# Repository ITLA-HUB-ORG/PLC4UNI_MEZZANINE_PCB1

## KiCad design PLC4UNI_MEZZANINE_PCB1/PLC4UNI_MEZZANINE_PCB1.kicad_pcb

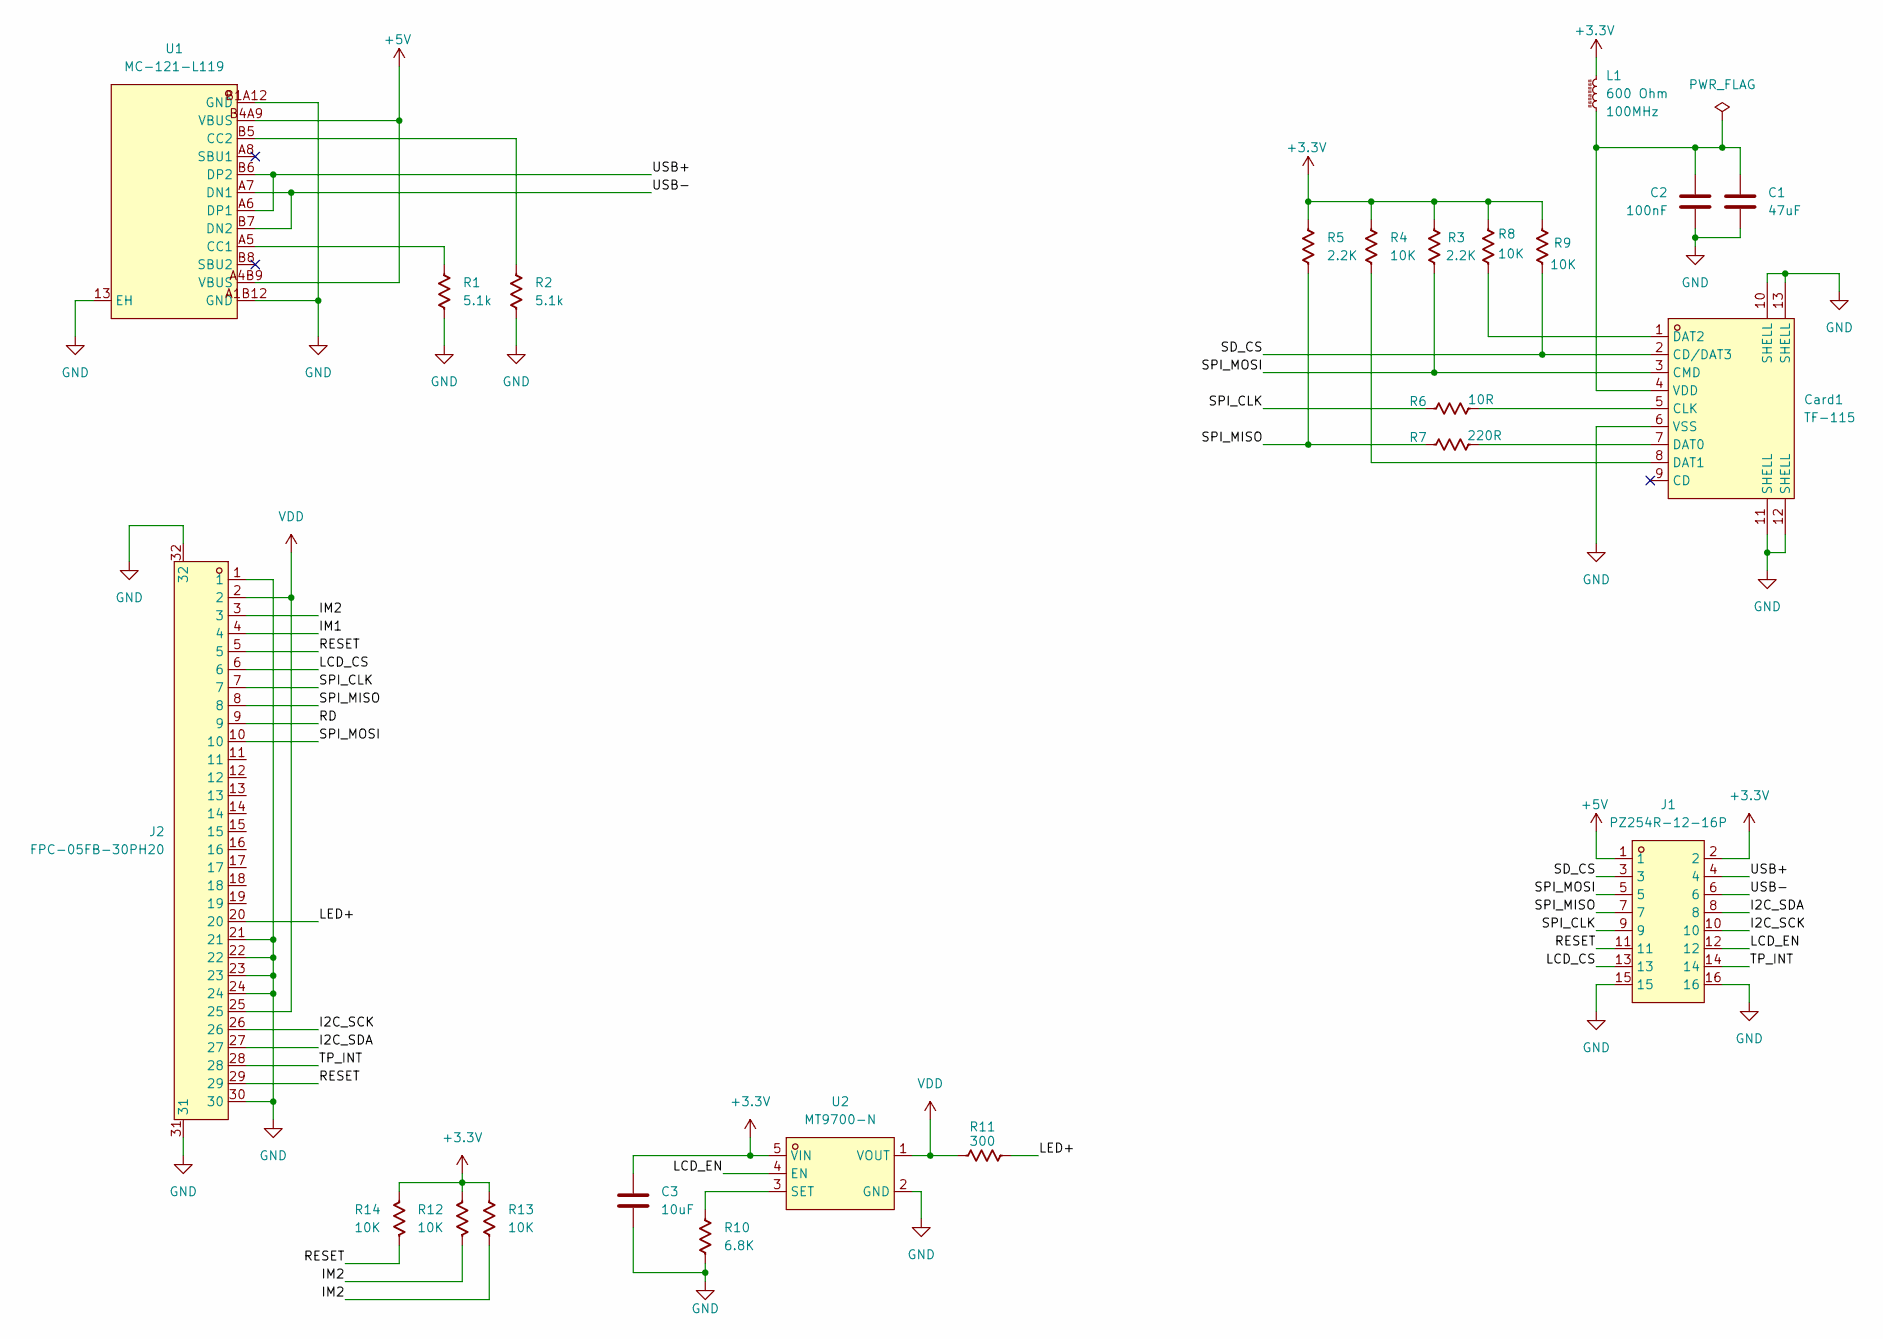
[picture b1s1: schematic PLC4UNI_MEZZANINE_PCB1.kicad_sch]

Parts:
C1: 47uF; C_0603_1608Metric
C2: 100nF; C_0603_1608Metric
C3: 10uF; C_0603_1608Metric
Card1: TF-115; TF-SMD_TF-115; LCSC Part C266620
J1: PZ254R-12-16P; HDR-TH_16P-P2.54-H-M-R2-C8-S2.54; LCSC Part C492436
J2: FPC-05FB-30PH20; FPC-SMD_30P-P0.50_FPC-05FB-30PH20; LCSC Part C2856833
L1: 600 Ohm; C_0805_2012Metric
R1, R2: 5.1k; R_0603_1608Metric
R3, R5: 2.2K; R_0603_1608Metric
R4, R8, R9, R12, R13, R14: 10K; R_0603_1608Metric
R6: 10R; R_0603_1608Metric
R7: 220R; R_0603_1608Metric
R10: 6.8K; R_0603_1608Metric
R11: 300; R_0603_1608Metric
U1: MC-121-L119; USB-C-SMD_HANBO_MC-121-L119; LCSC Part C6332278
U2: MT9700-N; SOT-23-5_L2.9-W1.6-P0.95-LS2.9-BL; LCSC Part C42441843

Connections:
+3.3V: C3.1, J1.2, L1.2, R3.1, R4.1, R5.1, R8.1, R9.1, R12.1, R13.1, R14.1, U2.5 (VIN)
+5V: J1.1, U1.A4B9 (VBUS), U1.B4A9 (VBUS)
/DB0: J2.11
/DB1: J2.12
/DB2: J2.13
/DB3: J2.14
/DB4: J2.15
/DB5: J2.16
/DB6: J2.17
/DB7: J2.18
/I2C_SCK: J1.10, J2.26
/I2C_SDA: J1.8, J2.27
/IM1: J2.4
/IM2: J2.3, R12.2, R13.2
/LCD_CS: J1.13, J2.6
/LCD_EN: J1.12, U2.4 (EN)
/LED+: J2.20, R11.2
/RD: J2.9
/RESET: J1.11, J2.5, J2.29, R14.2
/SD_CS: Card1.2 (CD/DAT3), J1.3, R9.2
/SPI_CLK: J1.9, J2.7, R6.1
/SPI_MOSI: Card1.3 (CMD), J1.5, J2.10, R3.2
/TP_INT: J1.14, J2.28
/USB+: J1.4, U1.A6 (DP1), U1.B6 (DP2)
/USB-: J1.6, U1.A7 (DN1), U1.B7 (DN2)
GND: C1.2, C2.2, C3.2, Card1.6 (VSS), Card1.10 (SHELL), Card1.11 (SHELL), Card1.12 (SHELL), Card1.13 (SHELL), J1.15, J1.16, J2.1, J2.21, J2.22, J2.23, J2.24, J2.30, J2.31, J2.32, R1.2, R2.2, R10.2, U1.13 (EH), U1.A1B12 (GND), U1.B1A12 (GND), U2.2 (GND)
unnamed: Card1.5 (CLK), R6.2
unnamed: Card1.7 (DAT0), R7.2
unnamed: Card1.8 (DAT1), R4.2
unnamed: Card1.1 (DAT2), R8.2
unnamed: C1.1, C2.1, Card1.4 (VDD), L1.1
unnamed: R1.1, U1.A5 (CC1)
unnamed: R2.1, U1.B5 (CC2)
unnamed: R10.1, U2.3 (SET)
VDD: J2.2, J2.25, R11.1, U2.1 (VOUT)

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
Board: 2 copper layers, 23 parts (0 on the bottom side), 26 nets, no tracks yet.

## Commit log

2026-03-07 Seleccionados los connectores Verificado el 3D
2026-03-13 Se cambio el conector J1 de 16 pines por un conector de 18 pines, para poder utilizar el display + touch en modo spi.
2026-03-19 Avances en esquemas y documentacion
2026-03-19 Cambio de etiqueta M1 M2
2026-03-20 Agragados circuitos de proteccion ESD
